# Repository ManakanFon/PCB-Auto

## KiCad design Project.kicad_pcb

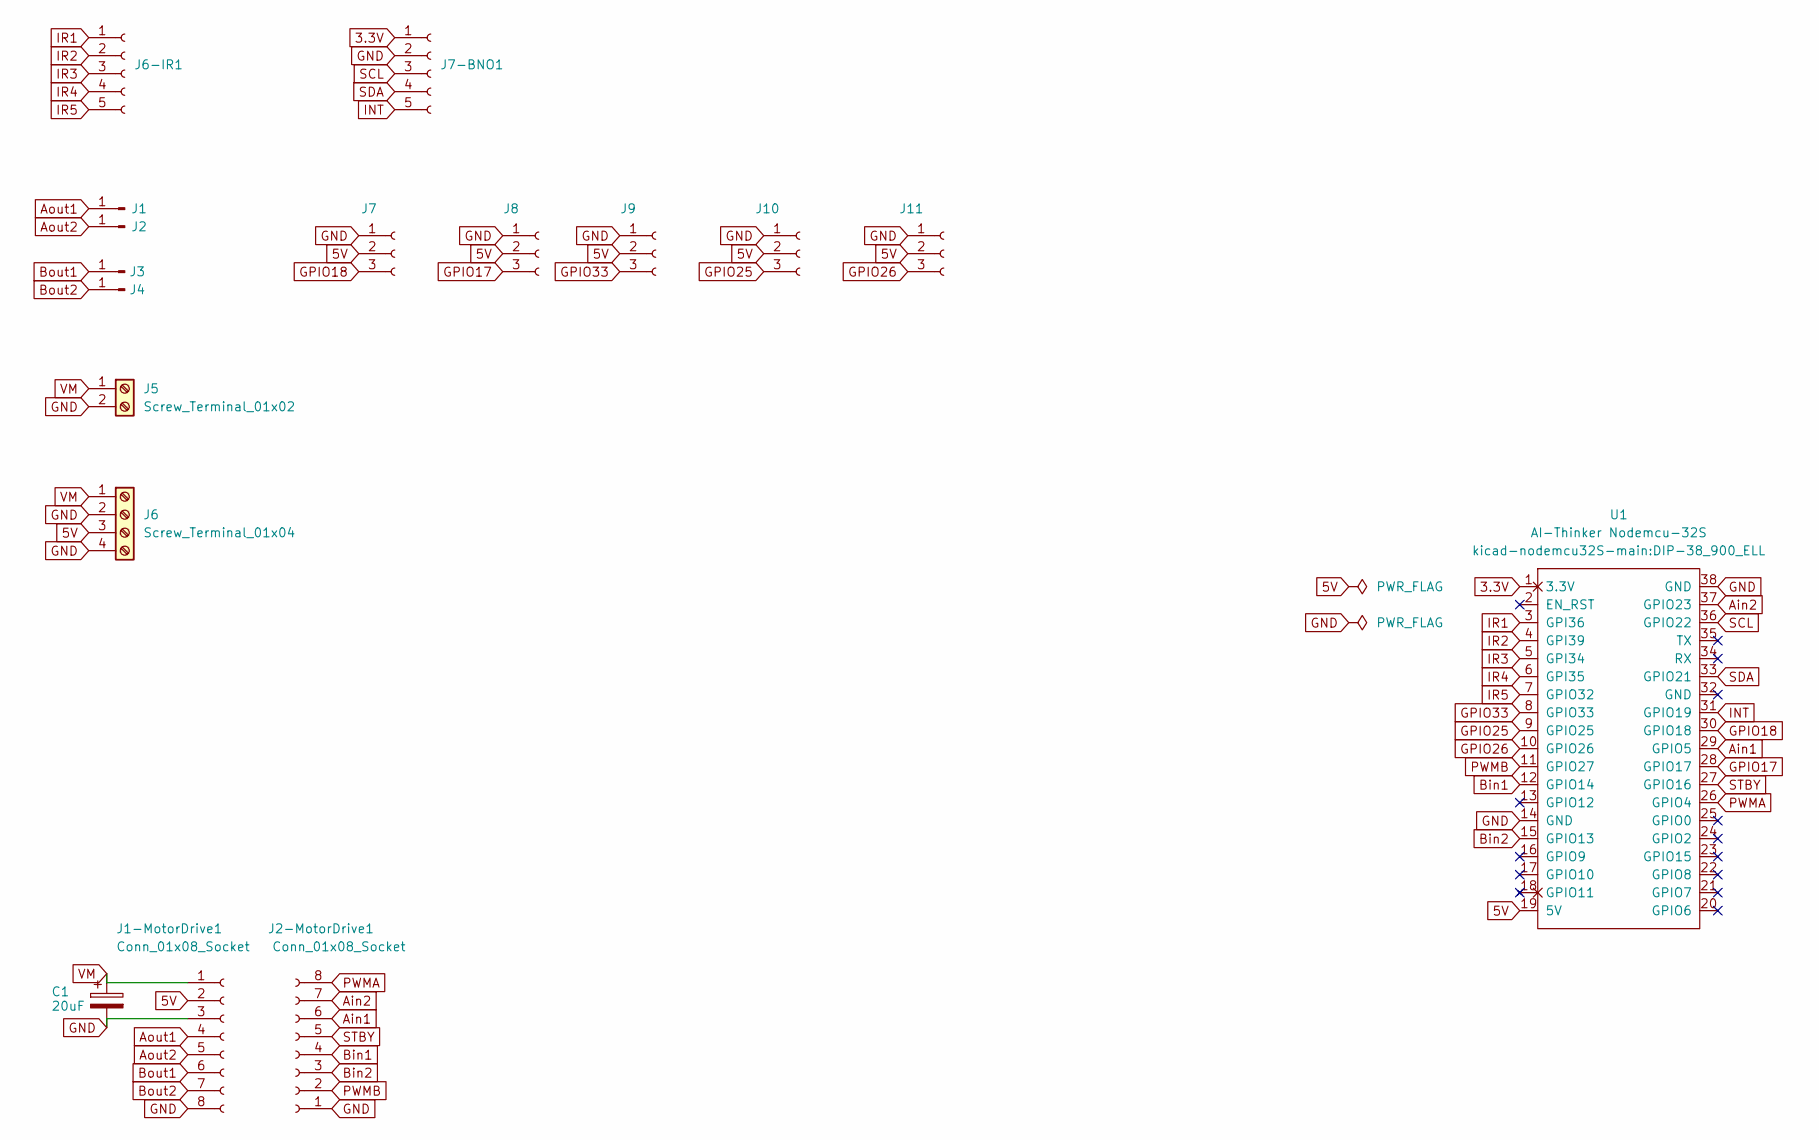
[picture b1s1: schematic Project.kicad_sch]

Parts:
C1: 20uF; CP_Radial_D10.0mm_P5.00mm
J1, J2, J3, J4: Conn_01x01_Pin; TestPoint_THTPad_D3.0mm_Drill1.5mm
J1-MotorDrive1, J2-MotorDrive1: Conn_01x08_Socket; PinHeader_1x08_P2.54mm_Vertical
J5: Screw_Terminal_01x02; TerminalBlock_4Ucon_1x02_P3.50mm_Vertical
J6: Screw_Terminal_01x04; YAAJ_DCDC_StepDown_LM2596
J6-IR1, J7-BNO1: Conn_01x05_Socket; PinHeader_1x05_P2.54mm_Vertical
J7, J8, J9, J10, J11: Conn_01x03_Socket; PinHeader_1x03_P2.54mm_Vertical
U1: AI-Thinker Nodemcu-32S; DIP-38_900_ELL

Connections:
3.3V: J7-BNO1.1, U1.1 (3.3V)
5V: J1-MotorDrive1.2, J6.3, J7.2, J8.2, J9.2, J10.2, J11.2, U1.19 (5V)
Ain1: J2-MotorDrive1.6, U1.29 (GPIO5)
Ain2: J2-MotorDrive1.7, U1.37 (GPIO23)
Aout1: J1.1 (Pin_1_1), J1-MotorDrive1.4
Aout2: J1-MotorDrive1.5, J2.1 (Pin_1_1)
Bin1: J2-MotorDrive1.4, U1.12 (GPIO14)
Bin2: J2-MotorDrive1.3, U1.15 (GPIO13)
Bout1: J1-MotorDrive1.6, J3.1 (Pin_1_1)
Bout2: J1-MotorDrive1.7, J4.1 (Pin_1_1)
GND: C1.2, J1-MotorDrive1.3, J1-MotorDrive1.8, J2-MotorDrive1.1, J5.2, J6.2, J6.4, J7.1, J7-BNO1.2, J8.1, J9.1, J10.1, J11.1, U1.14 (GND), U1.38 (GND)
GPIO17: J8.3, U1.28 (GPIO17)
GPIO18: J7.3, U1.30 (GPIO18)
GPIO25: J10.3, U1.9 (GPIO25)
GPIO26: J11.3, U1.10 (GPIO26)
GPIO33: J9.3, U1.8 (GPIO33)
INT: J7-BNO1.5, U1.31 (GPIO19)
IR1: J6-IR1.1, U1.3 (GPI36)
IR2: J6-IR1.2, U1.4 (GPI39)
IR3: J6-IR1.3, U1.5 (GPI34)
IR4: J6-IR1.4, U1.6 (GPI35)
IR5: J6-IR1.5, U1.7 (GPIO32)
PWMA: J2-MotorDrive1.8, U1.26 (GPIO4)
PWMB: J2-MotorDrive1.2, U1.11 (GPIO27)
SCL: J7-BNO1.3, U1.36 (GPIO22)
SDA: J7-BNO1.4, U1.33 (GPIO21)
STBY: J2-MotorDrive1.5, U1.27 (GPIO16)
VM: C1.1, J1-MotorDrive1.1, J5.1, J6.1

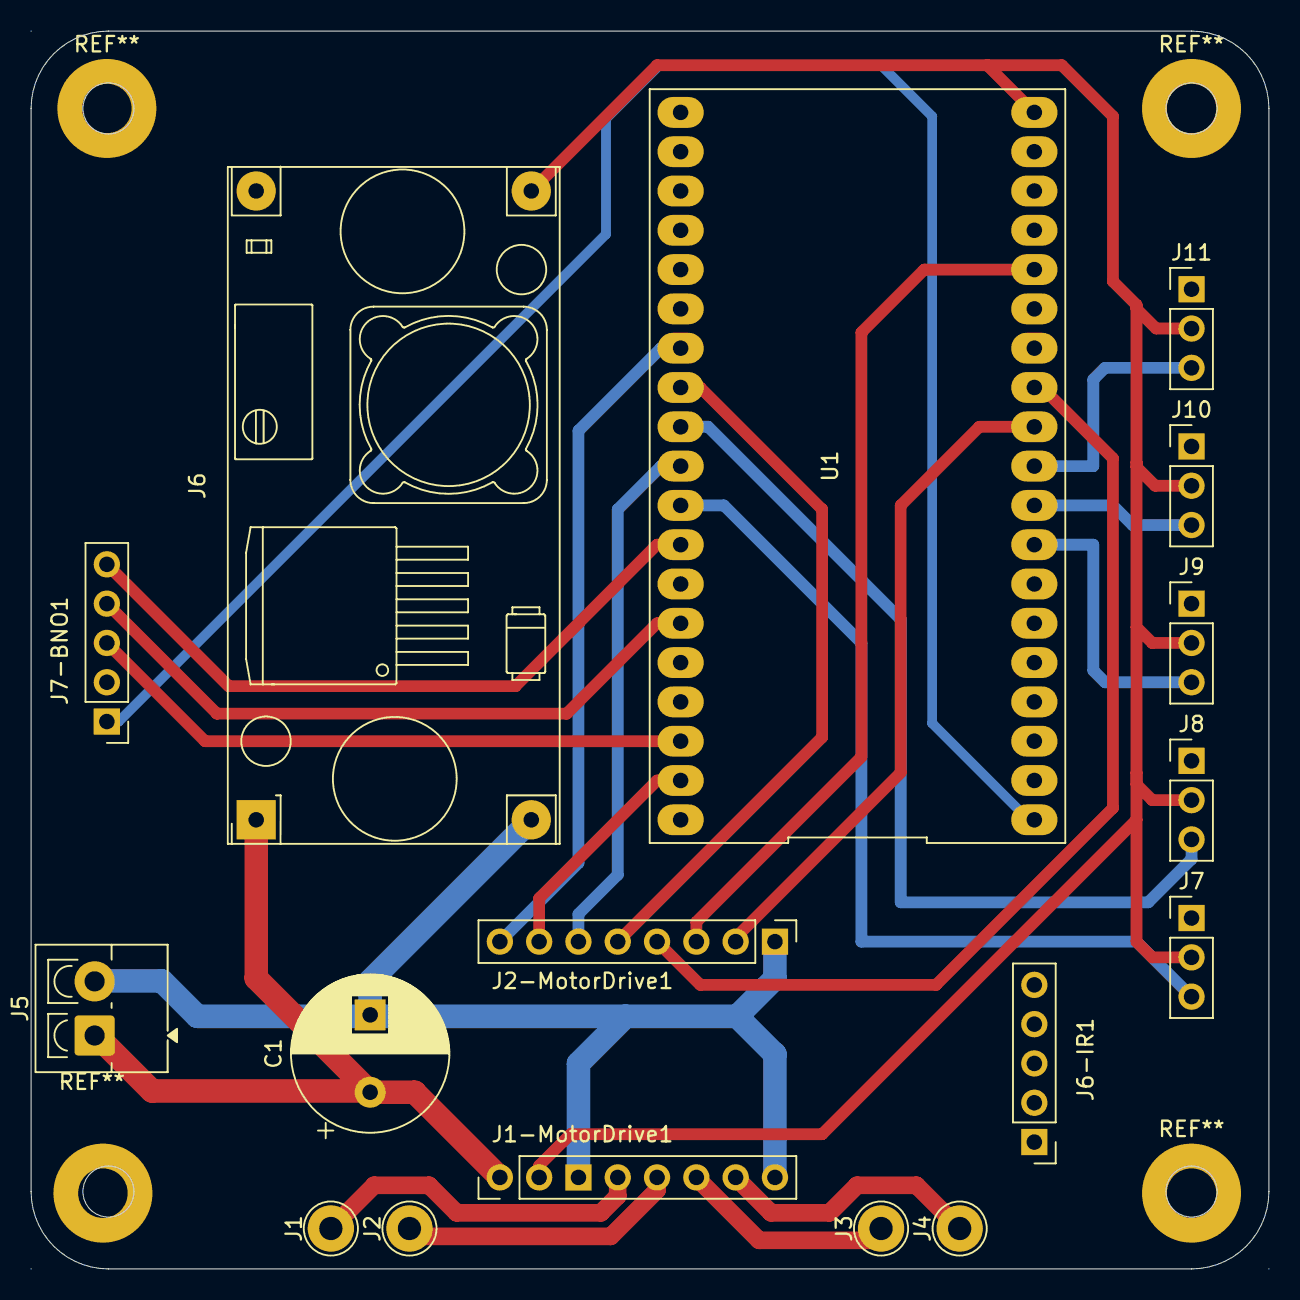
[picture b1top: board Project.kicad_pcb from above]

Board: 2 copper layers, 80.0 x 80.0 mm, 17 parts (0 on the bottom side), 28 nets.
